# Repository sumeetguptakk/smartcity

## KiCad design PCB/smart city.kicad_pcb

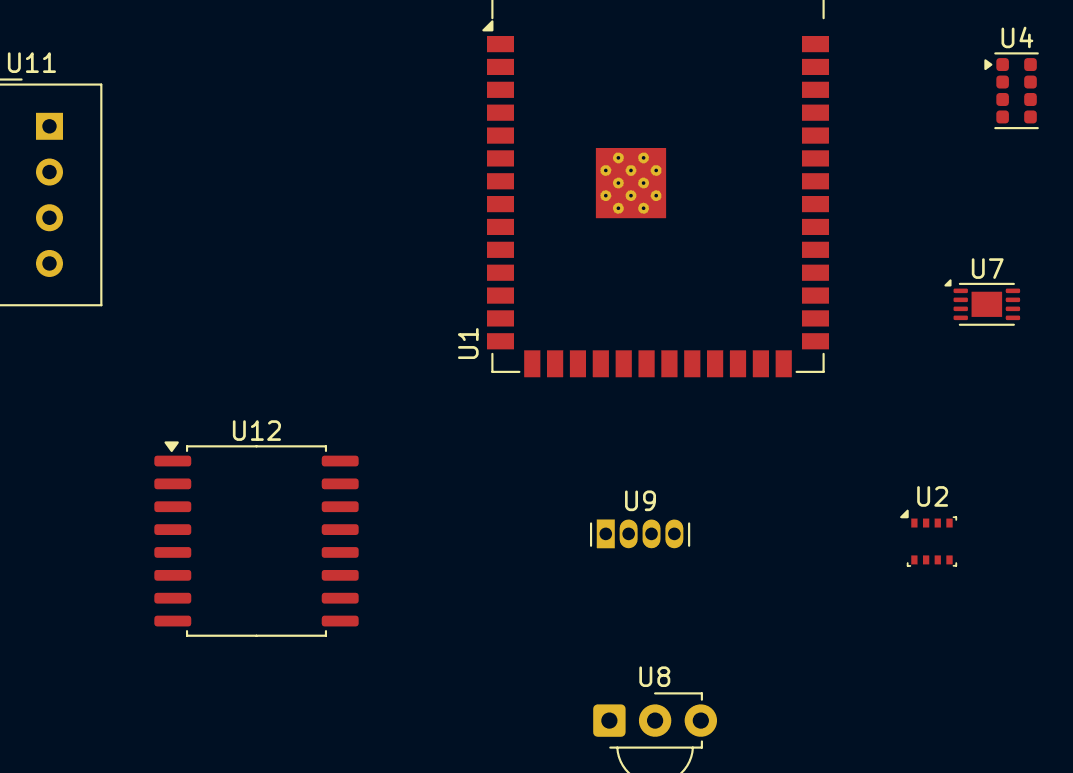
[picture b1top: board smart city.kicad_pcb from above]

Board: 2 copper layers, 8 parts (0 on the bottom side), 12 nets, no tracks yet.

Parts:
U1: ESP32-S3-WROOM-1
U2: BME280; Bosch_LGA-8_2.5x2.5mm_P0.65mm_ClockwisePinNumbering
U4: RPR-0521RS; Rohm_RPR-0521RS
U7: MCP73831-2-MC; DFN-8-1EP_3x2mm_P0.5mm_EP1.7x1.4mm
U8: TSSP58038; Vishay_MINICAST-3Pin
U9: A1363xKTTN-1; Allegro_SIP-4
U11: DHT11; Aosong_DHT11_5.5x12.0_P2.54mm
U12: DS3231M; SOIC-16W_7.5x10.3mm_P1.27mm

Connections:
+3.3V: U2.2 (CSB), U2.8 (VDD), U4.1 (VDD), U4.4 (LED_A), U11.1 (VDD), U12.2 (VCC)
+3V3: U1.2 (3V3), U1.13 (IO19), U7.1 (V_{DD}), U7.2 (V_{DD}), U8.3 (Vs), U9.1 (VCC)
GND: U1.1 (GND), U1.40 (GND), U1.41 (GND), U2.1 (GND), U2.5 (SDO), U2.7 (GND), U4.3 (GND), U4.5 (LED_K), U7.5 (STAT), U7.6 (V_{SS}), U7.8 (PROG), U8.2 (GND), U9.4 (GND), U11.4 (GND), U12.5 (GND), U12.6 (GND), U12.7 (GND), U12.8 (GND), U12.9 (GND), U12.10 (GND), U12.11 (GND), U12.12 (GND), U12.13 (GND)
unnamed: U1.4 (IO4), U9.2 (VOUT)
unnamed: U1.12 (IO8), U2.3 (SDI)
unnamed: U1.17 (IO9), U2.4 (SCK)
unnamed: U1.19 (IO11), U8.1 (OUT)
unnamed: U1.21 (IO13), U4.2 (SCL)
unnamed: U1.22 (IO14), U4.8 (SDA)
unnamed: U1.8 (IO15), U11.2 (DATA)
unnamed: U1.10 (IO17), U12.16 (SCL)
unnamed: U1.11 (IO18), U12.15 (SDA)

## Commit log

2025-03-08 Cad file uploading
2025-03-08 pcb and schematic
